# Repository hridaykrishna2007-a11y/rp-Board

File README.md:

# rpBoard

## ***A devboard powered by a rp2040 with a few neopixel led s to tinker with!***
This is a devboard thet runs on a rp2040 from Raspberry pi and has a 2x2 neopixel led matrix.

## ***PCB Design & Assembly***

This is a 2 layer PCB.  

**PCB FILES HERE:** [Link](https://github.com/hridaykrishna2007-a11y/rp-Board/tree/main/PCB)

## ***Schematics***  

## ***PCB Design***

## Why it was made?
This Project was made for Forge YSWS in Hack Club ( THANK YOU HACK CLUB <3 )

## HOW TO BUILD THIS PROJECT:  
Easy Peasy.
- Order the parts from the BOM and get the pcb fabricated too!
- Solder the components on the pcb and keep the orientations in mind (or you are cooked).
- Check the solder connections to prevent the board or the rp2040 microcontroller from going POOF.
- upload your code (or the sample one in this same repo) using usb cable and arduino ide.
- ITS READYYYYYYYYYYYYYYYYYYYYYY!

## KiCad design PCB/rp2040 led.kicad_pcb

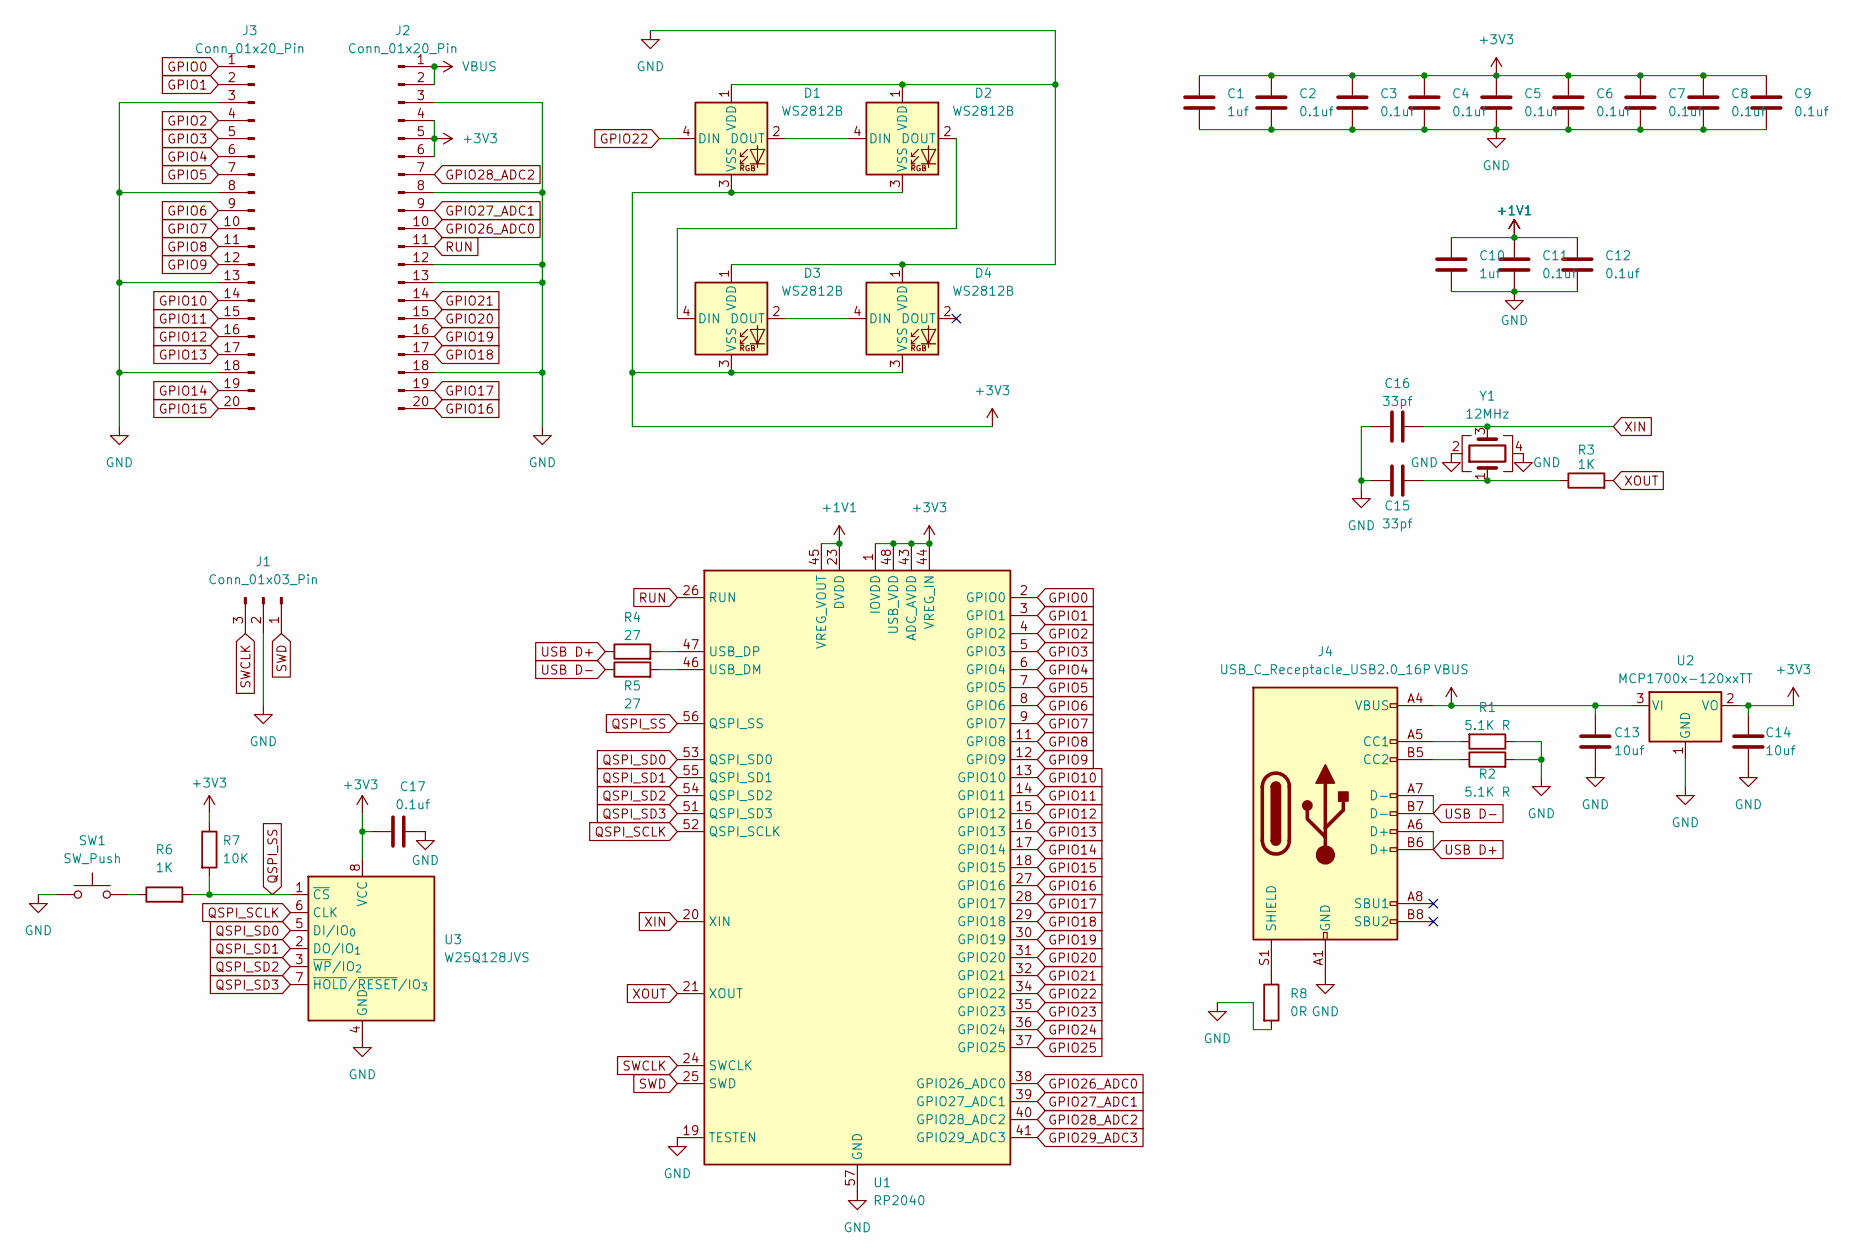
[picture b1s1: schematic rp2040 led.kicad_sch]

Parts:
C1, C10: 1uf; C_0603_1608Metric_Pad1.08x0.95mm_HandSolder
C2, C3, C4, C5, C6, C7, C8, C9, C11, C12, C17: 0.1uf; C_0603_1608Metric_Pad1.08x0.95mm_HandSolder
C13, C14: 10uf; C_0603_1608Metric_Pad1.08x0.95mm_HandSolder
C15, C16: 33pf; C_0603_1608Metric_Pad1.08x0.95mm_HandSolder
D1, D2, D3, D4: WS2812B; LED_WS2812B_PLCC4_5.0x5.0mm_P3.2mm
J1: Conn_01x03_Pin; PinHeader_1x03_P2.54mm_Vertical
J2, J3: Conn_01x20_Pin; PinHeader_1x20_P2.54mm_Vertical
J4: USB_C_Receptacle_USB2.0_16P; SHOUHAN_TYPE-C_16PIN_2MD__073_
R1, R2: 5.1K R; R_0603_1608Metric_Pad0.98x0.95mm_HandSolder
R3, R6: 1K; R_0603_1608Metric_Pad0.98x0.95mm_HandSolder
R4, R5: 27; R_0603_1608Metric_Pad0.98x0.95mm_HandSolder
R7: 10K; R_0603_1608Metric_Pad0.98x0.95mm_HandSolder
R8: 0R; R_0603_1608Metric_Pad0.98x0.95mm_HandSolder
SW1: SW_Push; SW_TS-1088-AR02016
U1: RP2040; QFN-56-1EP_7x7mm_P0.4mm_EP3.2x3.2mm
U2: MCP1700x-120xxTT; SOT-23
U3: W25Q128JVS; Winbond_USON-8-1EP_3x2mm_P0.5mm_EP0.2x1.6mm
Y1: 12MHz; Crystal_X322512MSB4SI

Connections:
+1V1: C10.1, C11.1, C12.1, U1.23 (DVDD), U1.45 (VREG_VOUT), U1.50 (DVDD)
+3V3: C1.2, C2.1, C3.1, C4.1, C5.1, C6.1, C7.1, C8.1, C9.1, C14.1, C17.1, D1.3 (VSS), D2.3 (VSS), D3.3 (VSS), D4.3 (VSS), J2.4, J2.5, J2.6, R7.1, U1.1 (IOVDD), U1.10 (IOVDD), U1.22 (IOVDD), U1.33 (IOVDD), U1.42 (IOVDD), U1.43 (ADC_AVDD), U1.44 (VREG_IN), U1.48 (USB_VDD), U1.49 (IOVDD), U2.2 (VO), U3.8 (VCC)
GND: C1.1, C2.2, C3.2, C4.2, C5.2, C6.2, C7.2, C8.2, C9.2, C10.2, C11.2, C12.2, C13.2, C14.2, C15.1, C16.1, C17.2, D1.1 (VDD), D2.1 (VDD), D3.1 (VDD), D4.1 (VDD), J1.2, J2.3, J2.8, J2.12, J2.13, J2.18, J3.3, J3.8, J3.13, J3.18, J4.A1 (GND), J4.A12 (GND), J4.B1 (GND), J4.B12 (GND), R1.1, R2.2, R8.2, SW1.1, U1.19 (TESTEN), U1.57 (GND), U2.1 (GND), U3.4 (GND), Y1.2, Y1.4
GPIO0: J3.1, U1.2 (GPIO0)
GPIO1: J3.2, U1.3 (GPIO1)
GPIO2: J3.4, U1.4 (GPIO2)
GPIO3: J3.5, U1.5 (GPIO3)
GPIO4: J3.6, U1.6 (GPIO4)
GPIO5: J3.7, U1.7 (GPIO5)
GPIO6: J3.9, U1.8 (GPIO6)
GPIO7: J3.10, U1.9 (GPIO7)
GPIO8: J3.11, U1.11 (GPIO8)
GPIO9: J3.12, U1.12 (GPIO9)
GPIO10: J3.14, U1.13 (GPIO10)
GPIO11: J3.15, U1.14 (GPIO11)
GPIO12: J3.16, U1.15 (GPIO12)
GPIO13: J3.17, U1.16 (GPIO13)
GPIO14: J3.19, U1.17 (GPIO14)
GPIO15: J3.20, U1.18 (GPIO15)
GPIO16: J2.20, U1.27 (GPIO16)
GPIO17: J2.19, U1.28 (GPIO17)
GPIO18: J2.17, U1.29 (GPIO18)
GPIO19: J2.16, U1.30 (GPIO19)
GPIO20: J2.15, U1.31 (GPIO20)
GPIO21: J2.14, U1.32 (GPIO21)
GPIO22: D1.4 (DIN), U1.34 (GPIO22)
GPIO23: U1.35 (GPIO23)
GPIO24: U1.36 (GPIO24)
GPIO25: U1.37 (GPIO25)
GPIO26_ADC0: J2.10, U1.38 (GPIO26_ADC0)
GPIO27_ADC1: J2.9, U1.39 (GPIO27_ADC1)
GPIO28_ADC2: J2.7, U1.40 (GPIO28_ADC2)
GPIO29_ADC3: U1.41 (GPIO29_ADC3)
unnamed: C15.2, R3.1, Y1.1
unnamed: D1.2 (DOUT), D2.4 (DIN)
unnamed: D2.2 (DOUT), D3.4 (DIN)
unnamed: D3.2 (DOUT), D4.4 (DIN)
unnamed: J4.A5 (CC1), R1.2
unnamed: J4.B5 (CC2), R2.1
unnamed: J4.S1 (SHIELD), R8.1
unnamed: R6.1, SW1.2
unnamed: R5.2, U1.46 (USB_DM)
unnamed: R4.2, U1.47 (USB_DP)
QSPI_SCLK: U1.52 (QSPI_SCLK), U3.6 (CLK)
QSPI_SD0: U1.53 (QSPI_SD0), U3.5 (DI/IO_{0})
QSPI_SD1: U1.55 (QSPI_SD1), U3.2 (DO/IO_{1})
QSPI_SD2: U1.54 (QSPI_SD2), U3.3 (~WP/IO_{2})
QSPI_SD3: U1.51 (QSPI_SD3), U3.7 (~HOLD/~RESET/IO_{3})
QSPI_SS: R6.2, R7.2, U1.56 (QSPI_SS), U3.1 (~CS)
RUN: J2.11, U1.26 (RUN)
SWCLK: J1.3, U1.24 (SWCLK)
SWD: J1.1, U1.25 (SWD)
USB D+: J4.A6 (D+), J4.B6 (D+), R4.1
USB D-: J4.A7 (D-), J4.B7 (D-), R5.1
VBUS: C13.1, J2.1, J2.2, J4.A4 (VBUS), J4.A9 (VBUS), J4.B4 (VBUS), J4.B9 (VBUS), U2.3 (VI)
XIN: C16.2, U1.20 (XIN), Y1.3
XOUT: R3.2, U1.21 (XOUT)

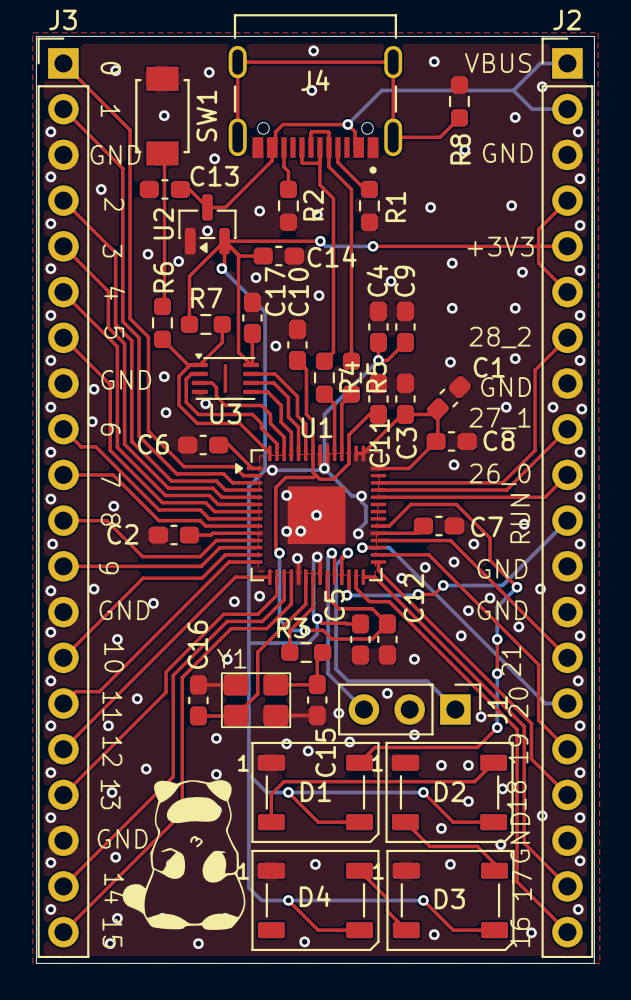
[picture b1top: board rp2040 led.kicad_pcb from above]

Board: 2 copper layers, 31.0 x 51.5 mm, 38 parts (0 on the bottom side), 53 nets.
